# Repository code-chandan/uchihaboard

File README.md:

# Uchiha Board

Uchiha Board is that one keyboard you wish you had ages ago  
It doesn’t try too hard, doesn’t scream gamer, doesn’t light up your whole desk  
It’s just smooth, clean, fast, and stupidly fun to use  
Looks simple but hits way harder than any of those overpriced store-bought keyboards  
Built from scratch, like actual start-to-finish grind, just because nothing else felt good enough

---

## how it started

It all kicked off during one of those random nights when the vibes were off and my keyboard just wasn’t giving  
Like I’m trying to get stuff done and the keyboard is out here lagging, flexing extra keys I don’t need, and feeling like a sponge  
So I closed everything, opened KiCad, and went full keyboard-goblin mode  
Started sketching out something that felt like mine  
Didn’t wanna go crazy with layout changes, so I stuck with something normal but fixed literally everything else

Redid the matrix from scratch so it’s way more responsive  
Kept the routing super clean  
Threw in hot swap sockets cause who’s got time for desoldering  
And yeah, gave it a solid case that doesn’t move unless you move it  
Now it’s this one-piece board that just works wherever  
At school, at home, in your bag, doesn’t matter  
Looks chill, performs like a beast  
And yeah it was a full solo mission because stock keyboards were too mid

---

## why i think it’s actually sick

So this board has MX support which basically means it’ll take any switch you throw at it  
Doesn’t split, doesn’t bend, doesn’t act weird  
Just a clean rectangle of power  
The layout is straight up solid, nothing extra, just full-row real estate for max typing flow

It runs on an elite-c which is literally one of the best things ever  
Firmware flashing is so easy it’s actually fun  
You could run QMK or VIA on this thing before your coffee even finishes brewing  
Rotary encoder support? Yup, added that too cause why not  
Matrix is tight, rows and columns are super balanced so typing feels like butter  
And the case? Fully 3D printable, no weird gaps, zero rattle, everything fits perfectly  
Honestly it’s not even just a keyboard, it’s a whole vibe

---

## what’s inside (BOM)

| Component          | Description                            | Qty | Price (USD) | Total |
|-------------------|----------------------------------------|-----|-------------|-------|
| elite-c            | handles everything like a champ         | 1   | 12.00        | 12.00  |
| MX switches        | your clicky friends                     | 45  | 0.35        | 15.75 |
| Keycaps            | one good set, no mix-match nonsense     | 1   | 20.00       | 20.00 |
| Diodes             | 1N4148, classic matrix stuff            | 45  | 0.03        | 1.35  |
| Resistors          | for pullups and the encoder             | 10  | 0.05        | 0.50  |
| Rotary encoder     | spin spin click click                   | 1   | 3.00        | 3.00  |
| PCB                | the actual custom-made heart of it all  | 1   | 30.00       | 30.00 |
| Acrylic case       | laser cut and clean                     | 1   | 15.00       | 15.00 |
| Screws & standoffs | hold it all together                    | 1   | 2.00        | 2.00  |
| Soldering stuff    | wire, solder, flux, all that jazz       | 1   | 3.00        | 3.00  |
| Random extras      | foam, rubber feet, labels               | 1   | 2.40        | 2.40  |

**Total cost** is somewhere around **$105.00**  
Not cheap but definitely not ridiculous for a full custom keyboard that doesn’t suck

---

## pics

| Image | What’s going on |
|-------|-----------------|
|  | clean and deadly |
|  | Schematic looking fresh, every row and column laid out like a pro |
|  | Full 3D render with switches and case, all ready to go |
|  | side view |
|  | side view |
|  | top view |

---

## license thingy

MIT License  
You can fork it, remix it, sell it, mod it, show it off at school, whatever  
Just don’t be that person who locks it up or pretends they made it from scratch  
Be chill

---

If you want this board, build it  
If you want to improve it, go wild  
Just don’t sleep on it  
Uchiha Board’s real

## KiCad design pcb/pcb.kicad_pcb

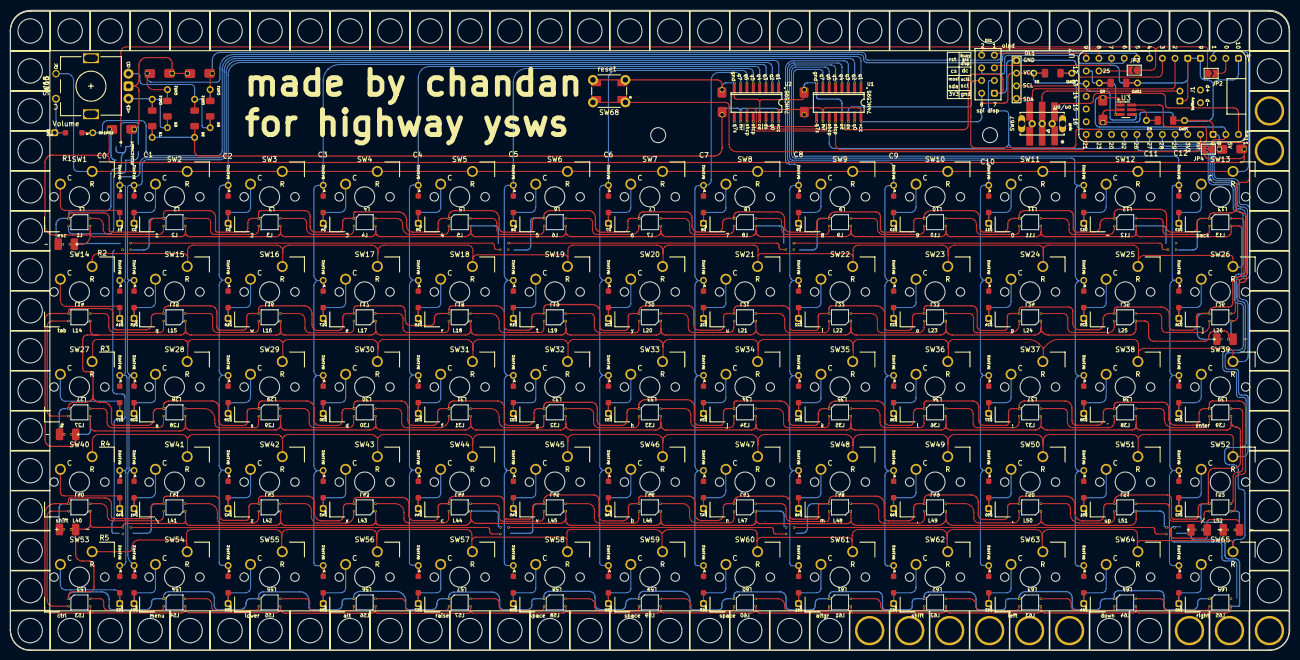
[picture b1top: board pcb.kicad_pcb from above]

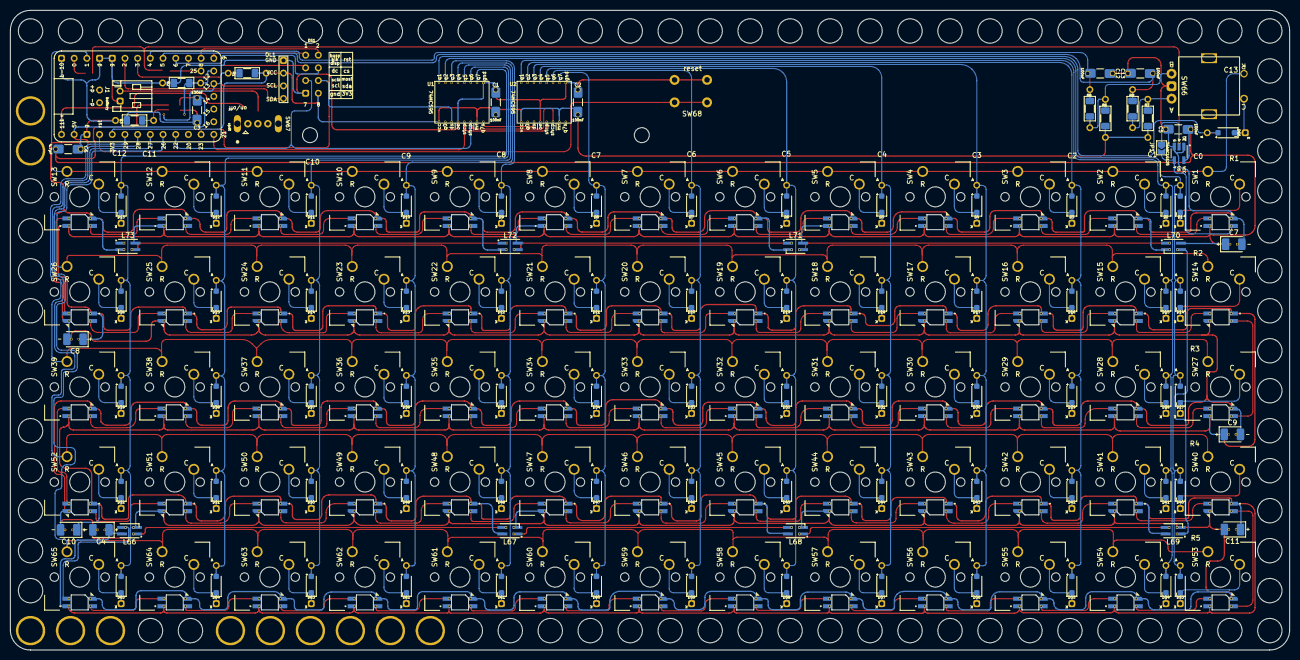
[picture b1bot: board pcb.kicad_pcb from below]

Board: 2 copper layers, 256.0 x 128.0 mm, 240 parts (161 on the bottom side), 185 nets.

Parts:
C1, C2, C3, C5, C12, C13: 100nF; C-1206_3216Metric_Pad1.33x1.80mm_HandSolder-long
C4, C7, C8, C9, C10, C11: 100µF; tantalum-3528
C6: 4.7µF; C-1206_3216Metric_Pad1.33x1.80mm_HandSolder-long
D1, D2, D3, D4, D5, D6, D7, D8, D9, D10, D11, D12, D13, D14, D15, D16, D17, D18, D19, D20, D21, D22, D23, D24, D25, D26, D27, D28, D29, D30, D31, D32, D33, D34, D35, D36, D37, D38, D39, D40, D41, D42, D43, D44, D45, D46, D47, D48, D49, D50, D51, D52, D53, D54, D55, D56, D57, D58, D59, D60, D61, D62, D63, D64, D65, D66: 1N4148; D_DO-35-SOD-123
DS1: spi disp; spi-eink-rgb-sharp
H1: MountingHole; LegoHole_16-32u_4875-rev12
J1: battery; battery connector - no surface
JP1, JP4: led; SolderJumper-Open
JP2: led1; SolderJumper-Open
JP3: led2; SolderJumper-Open
L1, L2, L3, L4, L5, L6, L7, L8, L9, L10, L11, L12, L13, L14, L15, L16, L17, L18, L19, L20, L21, L22, L23, L24, L25, L26, L27, L28, L29, L30, L31, L32, L33, L34, L35, L36, L37, L38, L39, L40, L41, L42, L43, L44, L45, L46, L47, L48, L49, L50, L51, L52, L53, L54, L55, L56, L57, L58, L59, L60, L61, L62, L63, L64, L65: SK6803; SK6812-MINI-E-pins
L66, L67, L68, L69, L70, L71, L72, L73: SK6805; SK6805_PLCC4_2.4x2.7mm_P1.3mm
OL1: oled; OLED_128x32
R1, R2, R6, R7, R8, R9: 10kΩ; R-dual-10k
R3: 75kΩ; R-dual-75k
SW1: esc; SW_Cherry_MX_1.00u_PCB
SW2: 1; SW_Cherry_MX_1.00u_PCB
SW3: 2; SW_Cherry_MX_1.00u_PCB
SW4: 3; SW_Cherry_MX_1.00u_PCB
SW5: 4; SW_Cherry_MX_1.00u_PCB
SW6: 5; SW_Cherry_MX_1.00u_PCB
SW7: 6; SW_Cherry_MX_1.00u_PCB
SW8: 7; SW_Cherry_MX_1.00u_PCB
SW9: 8; SW_Cherry_MX_1.00u_PCB
SW10: 9; SW_Cherry_MX_1.00u_PCB
SW11: 0; SW_Cherry_MX_1.00u_PCB
SW12: -; SW_Cherry_MX_1.00u_PCB-3d
SW13: back; SW_Cherry_MX_1.00u_PCB-3d
SW14: tab; SW_Cherry_MX_1.00u_PCB
SW15: q; SW_Cherry_MX_1.00u_PCB
SW16: w; SW_Cherry_MX_1.00u_PCB
SW17: e; SW_Cherry_MX_1.00u_PCB
SW18: r; SW_Cherry_MX_1.00u_PCB
SW19: t; SW_Cherry_MX_1.00u_PCB
SW20: y; SW_Cherry_MX_1.00u_PCB
SW21: u; SW_Cherry_MX_1.00u_PCB
SW22: i; SW_Cherry_MX_1.00u_PCB
SW23: o; SW_Cherry_MX_1.00u_PCB
SW24: p; SW_Cherry_MX_1.00u_PCB
SW25: [; SW_Cherry_MX_1.00u_PCB-3d
SW26: ]; SW_Cherry_MX_1.00u_PCB-3d
SW27: #; SW_Cherry_MX_1.00u_PCB
SW28: a; SW_Cherry_MX_1.00u_PCB
SW29: s; SW_Cherry_MX_1.00u_PCB
SW30: d; SW_Cherry_MX_1.00u_PCB
SW31: f; SW_Cherry_MX_1.00u_PCB
SW32: g; SW_Cherry_MX_1.00u_PCB
SW33: h; SW_Cherry_MX_1.00u_PCB
SW34: j; SW_Cherry_MX_1.00u_PCB
SW35: k; SW_Cherry_MX_1.00u_PCB
SW36: l; SW_Cherry_MX_1.00u_PCB
SW37: ;; SW_Cherry_MX_1.00u_PCB
SW38: '; SW_Cherry_MX_1.00u_PCB-3d
SW39: enter; SW_Cherry_MX_1.00u_PCB-3d
SW40, SW62: shift; SW_Cherry_MX_1.00u_PCB
SW41: \; SW_Cherry_MX_1.00u_PCB
SW42: z; SW_Cherry_MX_1.00u_PCB
SW43: x; SW_Cherry_MX_1.00u_PCB
SW44: c; SW_Cherry_MX_1.00u_PCB
SW45: v; SW_Cherry_MX_1.00u_PCB
SW46: b; SW_Cherry_MX_1.00u_PCB
SW47: n; SW_Cherry_MX_1.00u_PCB
SW48: m; SW_Cherry_MX_1.00u_PCB
SW49: ,; SW_Cherry_MX_1.00u_PCB
SW50: .; SW_Cherry_MX_1.00u_PCB
SW51: up; SW_Cherry_MX_1.00u_PCB-3d
SW52: /; SW_Cherry_MX_1.00u_PCB-3d
SW53: ctrl; SW_Cherry_MX_1.00u_PCB
SW54: menu; SW_Cherry_MX_1.00u_PCB
SW55: lower; SW_Cherry_MX_1.00u_PCB
SW56: alt; SW_Cherry_MX_1.00u_PCB
SW57: raise; SW_Cherry_MX_1.00u_PCB
SW58, SW59, SW60: space; SW_Cherry_MX_1.00u_PCB
SW61: altgr; SW_Cherry_MX_1.00u_PCB
SW63: left; SW_Cherry_MX_1.00u_PCB-3d
SW64: down; SW_Cherry_MX_1.00u_PCB-3d
SW65: right; SW_Cherry_MX_1.00u_PCB-3d
SW66: Volume; RotaryEncoder_Alps_EC11E_Vertical_H20mm
SW67: on/off; switch_slide
SW68: reset; SW_reset
U1, U2: 74HC595; 74HC595-sop16
U3: TPS2553DBVR; SOT-23-6-reg
U5: 74AHC1G125; 74AHC1G125-sot23-v2
U7: pm like - Helios; Helios_tht

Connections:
3v3: C1.2, C2.2, DS1.8 (VCC), OL1.3 (VCC), R1.1, R6.1, R7.1, U1.10 (~SRCLR), U1.16 (VCC), U2.10 (~SRCLR), U2.16 (VCC), U7.16 (3V3)
5V: C3.2, JP4.1 (A), U3.1 (IN), U7.13 (5V)
unnamed: D1.1 (K), SW1.2
unnamed: D2.1 (K), SW2.2
unnamed: D3.1 (K), SW3.2
unnamed: D4.1 (K), SW4.2
unnamed: D5.1 (K), SW5.2
unnamed: D6.1 (K), SW6.2
unnamed: D7.1 (K), SW7.2
unnamed: D8.1 (K), SW8.2
unnamed: D9.1 (K), SW9.2
unnamed: D10.1 (K), SW10.2
unnamed: D11.1 (K), SW11.2
unnamed: D12.1 (K), SW12.2
unnamed: D13.1 (K), SW13.2
unnamed: D14.1 (K), SW14.2
unnamed: D15.1 (K), SW15.2
unnamed: D16.1 (K), SW16.2
unnamed: D17.1 (K), SW17.2
unnamed: D18.1 (K), SW18.2
unnamed: D19.1 (K), SW19.2
unnamed: D20.1 (K), SW20.2
unnamed: D21.1 (K), SW21.2
unnamed: D22.1 (K), SW22.2
unnamed: D23.1 (K), SW23.2
unnamed: D24.1 (K), SW24.2
unnamed: D25.1 (K), SW25.2
unnamed: D26.1 (K), SW26.2
unnamed: D27.1 (K), SW27.2
unnamed: D28.1 (K), SW28.2
unnamed: D29.1 (K), SW29.2
unnamed: D30.1 (K), SW30.2
unnamed: D31.1 (K), SW31.2
unnamed: D32.1 (K), SW32.2
unnamed: D33.1 (K), SW33.2
unnamed: D34.1 (K), SW34.2
unnamed: D35.1 (K), SW35.2
unnamed: D36.1 (K), SW36.2
unnamed: D37.1 (K), SW37.2
unnamed: D38.1 (K), SW38.2
unnamed: D39.1 (K), SW39.2
unnamed: D40.1 (K), SW40.2
unnamed: D41.1 (K), SW41.2
unnamed: D42.1 (K), SW42.2
unnamed: D43.1 (K), SW43.2
unnamed: D44.1 (K), SW44.2
unnamed: D45.1 (K), SW45.2
unnamed: D46.1 (K), SW46.2
unnamed: D47.1 (K), SW47.2
unnamed: D48.1 (K), SW48.2
unnamed: D49.1 (K), SW49.2
unnamed: D50.1 (K), SW50.2
unnamed: D51.1 (K), SW51.2
unnamed: D52.1 (K), SW52.2
unnamed: D53.1 (K), SW53.2
unnamed: D54.1 (K), SW54.2
unnamed: D55.1 (K), SW55.2
unnamed: D56.1 (K), SW56.2
unnamed: D57.1 (K), SW57.2
unnamed: D58.1 (K), SW58.2
unnamed: D59.1 (K), SW59.2
unnamed: D60.1 (K), SW60.2
unnamed: D61.1 (K), SW61.2
unnamed: D62.1 (K), SW62.2
unnamed: D63.1 (K), SW63.2
unnamed: D64.1 (K), SW64.2
unnamed: D65.1 (K), SW65.2
unnamed: D66.1 (K), SW66.S1
unnamed: L1.2 (DOUT), L2.4 (DIN)
unnamed: L2.2 (DOUT), L3.4 (DIN)
unnamed: L3.2 (DOUT), L4.4 (DIN)
unnamed: L4.2 (DOUT), L5.4 (DIN)
unnamed: L5.2 (DOUT), L6.4 (DIN)
unnamed: L6.2 (DOUT), L7.4 (DIN)
unnamed: L7.2 (DOUT), L8.4 (DIN)
unnamed: L8.2 (DOUT), L9.4 (DIN)
unnamed: L9.2 (DOUT), L10.4 (DIN)
unnamed: L10.2 (DOUT), L11.4 (DIN)
unnamed: L11.2 (DOUT), L12.4 (DIN)
unnamed: L12.2 (DOUT), L13.4 (DIN)
unnamed: L13.2 (DOUT), L26.4 (DIN)
unnamed: L14.4 (DIN), L15.2 (DOUT)
unnamed: L14.2 (DOUT), L27.4 (DIN)
unnamed: L15.4 (DIN), L16.2 (DOUT)
unnamed: L16.4 (DIN), L17.2 (DOUT)
unnamed: L17.4 (DIN), L18.2 (DOUT)
unnamed: L18.4 (DIN), L19.2 (DOUT)
unnamed: L19.4 (DIN), L20.2 (DOUT)
unnamed: L20.4 (DIN), L21.2 (DOUT)
unnamed: L21.4 (DIN), L22.2 (DOUT)
unnamed: L22.4 (DIN), L23.2 (DOUT)
unnamed: L23.4 (DIN), L24.2 (DOUT)
unnamed: L24.4 (DIN), L25.2 (DOUT)
unnamed: L25.4 (DIN), L26.2 (DOUT)
unnamed: L27.2 (DOUT), L28.4 (DIN)
unnamed: L28.2 (DOUT), L29.4 (DIN)
unnamed: L29.2 (DOUT), L30.4 (DIN)
unnamed: L30.2 (DOUT), L31.4 (DIN)
unnamed: L31.2 (DOUT), L32.4 (DIN)
unnamed: L32.2 (DOUT), L33.4 (DIN)
unnamed: L33.2 (DOUT), L34.4 (DIN)
unnamed: L34.2 (DOUT), L35.4 (DIN)
unnamed: L35.2 (DOUT), L36.4 (DIN)
unnamed: L36.2 (DOUT), L37.4 (DIN)
unnamed: L37.2 (DOUT), L38.4 (DIN)
unnamed: L38.2 (DOUT), L39.4 (DIN)
unnamed: L39.2 (DOUT), L52.4 (DIN)
unnamed: L40.4 (DIN), L41.2 (DOUT)
unnamed: L40.2 (DOUT), L53.4 (DIN)
unnamed: L41.4 (DIN), L42.2 (DOUT)
unnamed: L42.4 (DIN), L43.2 (DOUT)
unnamed: L43.4 (DIN), L44.2 (DOUT)
unnamed: L44.4 (DIN), L45.2 (DOUT)
unnamed: L45.4 (DIN), L46.2 (DOUT)
unnamed: L46.4 (DIN), L47.2 (DOUT)
unnamed: L47.4 (DIN), L48.2 (DOUT)
unnamed: L48.4 (DIN), L49.2 (DOUT)
unnamed: L49.4 (DIN), L50.2 (DOUT)
unnamed: L50.4 (DIN), L51.2 (DOUT)
unnamed: L51.4 (DIN), L52.2 (DOUT)
unnamed: L53.2 (DOUT), L54.4 (DIN)
unnamed: L54.2 (DOUT), L55.4 (DIN)
unnamed: L55.2 (DOUT), L56.4 (DIN)
unnamed: L56.2 (DOUT), L57.4 (DIN)
unnamed: L57.2 (DOUT), L58.4 (DIN)
unnamed: L58.2 (DOUT), L59.4 (DIN)
unnamed: L59.2 (DOUT), L60.4 (DIN)
unnamed: L60.2 (DOUT), L61.4 (DIN)
unnamed: L61.2 (DOUT), L62.4 (DIN)
unnamed: L62.2 (DOUT), L63.4 (DIN)
unnamed: L63.2 (DOUT), L64.4 (DIN)
unnamed: L64.2 (DOUT), L65.4 (DIN)
unnamed: L65.2 (DOUT), L66.3 (DIN)
unnamed: L66.1 (DOUT), L67.3 (DIN)
unnamed: L67.1 (DOUT), L68.3 (DIN)
unnamed: L68.1 (DOUT), L69.3 (DIN)
unnamed: L69.1 (DOUT), L70.3 (DIN)
unnamed: L70.1 (DOUT), L71.3 (DIN)
unnamed: L71.1 (DOUT), L72.3 (DIN)
unnamed: L72.1 (DOUT), L73.3 (DIN)
unnamed: R3.1, U3.5 (ILIM)
bat+: J1.1, SW67.2 (B)
blk: DS1.1 (busy), U7.12 (P9)
c0: D1.2 (A), D14.2 (A), D27.2 (A), D40.2 (A), D53.2 (A), U1.2 (QC)
c1: D2.2 (A), D15.2 (A), D28.2 (A), D41.2 (A), D54.2 (A), U2.1 (QB)
c2: D3.2 (A), D16.2 (A), D29.2 (A), D42.2 (A), D55.2 (A), U2.2 (QC)
c3: D4.2 (A), D17.2 (A), D30.2 (A), D43.2 (A), D56.2 (A), U2.3 (QD)
c4: D5.2 (A), D18.2 (A), D31.2 (A), D44.2 (A), D57.2 (A), U2.4 (QE)
c5: D6.2 (A), D19.2 (A), D32.2 (A), D45.2 (A), D58.2 (A), U2.5 (QF)
c6: D7.2 (A), D20.2 (A), D33.2 (A), D46.2 (A), D59.2 (A), U2.6 (QG)
c7: D8.2 (A), D21.2 (A), D34.2 (A), D47.2 (A), D60.2 (A), U2.7 (QH)
c8: D9.2 (A), D22.2 (A), D35.2 (A), D48.2 (A), D61.2 (A), U1.3 (QD)
c9: D10.2 (A), D23.2 (A), D36.2 (A), D49.2 (A), D62.2 (A), U1.4 (QE)
c10: D11.2 (A), D24.2 (A), D37.2 (A), D50.2 (A), D63.2 (A), U1.5 (QF)
c11: D12.2 (A), D25.2 (A), D38.2 (A), D51.2 (A), D64.2 (A), U1.6 (QG)
c12: D13.2 (A), D26.2 (A), D39.2 (A), D52.2 (A), D65.2 (A), U1.7 (QH)
c13: D66.2 (A), U1.1 (QB)
clock: DS1.5 (scl), U1.11 (SRCLK), U2.11 (SRCLK), U7.21 (P22)
cs: U1.12 (RCLK), U2.12 (RCLK), U7.24 (P21)
cs_disp: DS1.4 (CS), U7.9 (P6)
dc: DS1.3 (d/c), U7.10 (P7)
ea: R7.2, R9.1, SW66.A
eb: R6.2, R8.1, SW66.B
ext+: SW67.1 (A), U7.30 (P11)
fault: R1.2, U3.4 (~FAULT), U7.26 (P13)
gnd: C1.1, C2.1, C3.1, C4.2, C5.1, C6.1, C7.2, C8.2, C9.2, C10.2, C11.2, C12.1, C13.1, DS1.7 (GND), J1.2, L1.3 (G), L2.3 (G), L3.3 (G), L4.3 (G), L5.3 (G), L6.3 (G), L7.3 (G), L8.3 (G), L9.3 (G), L10.3 (G), L11.3 (G), L12.3 (G), L13.3 (G), L14.3 (G), L15.3 (G), L16.3 (G), L17.3 (G), L18.3 (G), L19.3 (G), L20.3 (G), L21.3 (G), L22.3 (G), L23.3 (G), L24.3 (G), L25.3 (G), L26.3 (G), L27.3 (G), L28.3 (G), L29.3 (G), L30.3 (G), L31.3 (G), L32.3 (G), L33.3 (G), L34.3 (G), L35.3 (G), L36.3 (G), L37.3 (G), L38.3 (G), L39.3 (G), L40.3 (G), L41.3 (G), L42.3 (G), L43.3 (G), L44.3 (G), L45.3 (G), L46.3 (G), L47.3 (G), L48.3 (G), L49.3 (G), L50.3 (G), L51.3 (G), L52.3 (G), L53.3 (G), L54.3 (G), L55.3 (G), L56.3 (G), L57.3 (G), L58.3 (G), L59.3 (G), L60.3 (G), L61.3 (G), L62.3 (G), L63.3 (G), L64.3 (G), L65.3 (G), L66.2 (VSS), L67.2 (VSS), L68.2 (VSS), L69.2 (VSS), L70.2 (VSS), L71.2 (VSS), L72.2 (VSS), L73.2 (VSS), OL1.4 (GND), R2.2, R3.2, SW66.C, SW68.2 (B), U1.8 (GND), U1.13 (~OE), U2.8 (GND), U2.13 (~OE), U3.2 (GND), U5.1, U5.3 (GND), U7.3 (GND), U7.4 (GND), U7.14 (GND), U7.31 (P10)
l: JP1.1 (A), JP2.1 (A), JP3.1 (A), U5.2
l1: JP2.2 (B), U7.1 (P0)
l2: JP3.2 (B), U7.34 (P25)
led_EN: R2.1, U3.3 (EN), U7.25 (P12)
led_PWR: C4.1, C5.2, C6.2, C7.1, C8.1, C9.1, C10.1, C11.1, JP4.2 (B), L1.1 (5V), L2.1 (5V), L3.1 (5V), L4.1 (5V), L5.1 (5V), L6.1 (5V), L7.1 (5V), L8.1 (5V), L9.1 (5V), L10.1 (5V), L11.1 (5V), L12.1 (5V), L13.1 (5V), L14.1 (5V), L15.1 (5V), L16.1 (5V), L17.1 (5V), L18.1 (5V), L19.1 (5V), L20.1 (5V), L21.1 (5V), L22.1 (5V), L23.1 (5V), L24.1 (5V), L25.1 (5V), L26.1 (5V), L27.1 (5V), L28.1 (5V), L29.1 (5V), L30.1 (5V), L31.1 (5V), L32.1 (5V), L33.1 (5V), L34.1 (5V), L35.1 (5V), L36.1 (5V), L37.1 (5V), L38.1 (5V), L39.1 (5V), L40.1 (5V), L41.1 (5V), L42.1 (5V), L43.1 (5V), L44.1 (5V), L45.1 (5V), L46.1 (5V), L47.1 (5V), L48.1 (5V), L49.1 (5V), L50.1 (5V), L51.1 (5V), L52.1 (5V), L53.1 (5V), L54.1 (5V), L55.1 (5V), L56.1 (5V), L57.1 (5V), L58.1 (5V), L59.1 (5V), L60.1 (5V), L61.1 (5V), L62.1 (5V), L63.1 (5V), L64.1 (5V), L65.1 (5V), L66.4 (VDD), L67.4 (VDD), L68.4 (VDD), L69.4 (VDD), L70.4 (VDD), L71.4 (VDD), L72.4 (VDD), L73.4 (VDD), U3.6 (OUT), U5.5 (VCC)
ll: JP1.2 (B), L1.4 (DIN), U5.4
mea: C13.2, R9.2, U7.8 (P5)
meb: C12.2, R8.2, U7.7 (P4)
mosi: DS1.6 (sda), U1.14 (SER), U7.23
next: U1.9 (QH'), U2.14 (SER)
r1: SW1.1, SW2.1, SW3.1, SW4.1, SW5.1, SW6.1, SW7.1, SW8.1, SW9.1, SW10.1, SW11.1, SW12.1, SW13.1, SW66.S2, U7.2 (P1)
r2: SW14.1, SW15.1, SW16.1, SW17.1, SW18.1, SW19.1, SW20.1, SW21.1, SW22.1, SW23.1, SW24.1, SW25.1, SW26.1, U7.20 (P26)
r3: SW27.1, SW28.1, SW29.1, SW30.1, SW31.1, SW32.1, SW33.1, SW34.1, SW35.1, SW36.1, SW37.1, SW38.1, SW39.1, U7.17 (P29)
r4: SW40.1, SW41.1, SW42.1, SW43.1, SW44.1, SW45.1, SW46.1, SW47.1, SW48.1, SW49.1, SW50.1, SW51.1, SW52.1, U7.18 (P28)
r5: SW53.1, SW54.1, SW55.1, SW56.1, SW57.1, SW58.1, SW59.1, SW60.1, SW61.1, SW62.1, SW63.1, SW64.1, SW65.1, U7.19 (P27)
reset: SW68.1 (A), U7.15 (RST)
rst: DS1.2 (res), U7.11 (P8)
scl: OL1.2 (SCL), U7.6 (P3)
sda: OL1.1 (SDA), U7.5 (P2)
